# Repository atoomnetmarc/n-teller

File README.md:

# n-teller

n-teller is an IoT device that displays the number of [checked in participants and visitors](https://revspace.nl/N) at the hackerspace called [Revelation Space (or RevSpace)](https://revspace.nl).

It connects to the [RevSpace MQTT server](https://revspace.nl/MQTT) via WiFi using an ESP8266.

The MQTT server publishes to [a few topics of interest](https://revspace.nl/MQTT#Topics) that are subscribed:

- revspace/[doorduino](https://revspace.nl/Doorduino3)/checked-in: this is the current total checked people.
- revspace/[state](https://revspace.nl/Spacestatus): the current state (open or closed) of the hackerspace.

# Schematic

[hardware/n-teller-schematic.pdf](hardware/n-teller-schematic.pdf)

# BOM

See interactive BOM: [hardware/bom/](https://html-preview.github.io/?url=https://github.com/atoomnetmarc/n-teller/blob/main/hardware/bom/ibom.html)

You will also need:

- The pcb. See [hardware/gerber/](hardware/gerber/) for gerber files.
- 2x M3x12 BHCS screws.
- Optional 1x [USB Type-C Female Chassis Connector](USB%20Type-C%20Female%20Chassis%20Connector.jpg).

# Render

# 3d-print

In the [3d](3d/) directory you can find a stand for the pcb.

Print `n-teller-stand-w-usb-c-socket.stl`. This will fit the optional USB Type-C Female Chassis Connector mentioned in the BOM. Or print `n-teller-stand.stl` and roll your own connection to 5V power supply.

# Firmware

Compile and flash the firmware located in the [firmware directory](firmware/). You will need [PlatformIO](https://platformio.org/) for this. I recommend installing the [PlatformIO extension for VSCode](https://platformio.org/install/ide?install=vscode).

# Configure WiFi

Double press the reset button (somewhat slowly). The letters `AP` will appear on the display. Now connect to a WiFi network with a name like `nteller-bcddc2895fd2`. Then go to: http://192.168.4.1/ and configure your WiFi.

# Display information

PCB was designed to fit this type (pinout and dimensions) of 0.36" 4-digit 7-segment common cathode LED display:

## Model numbers and color options

| Model         | Color      | Tested             |
| ------------- | ---------- | ------------------ |
| LFD036AAG-101 | green      |
| 3461AB        | blue       | :heavy_check_mark: |
| 3461AG        | green      |
| 3461AGG       | jade green |
| 3461AO        | orange     |
| 3461AS        | red        |
| 3461AW        | white      |
| 3461AY        | yellow     |

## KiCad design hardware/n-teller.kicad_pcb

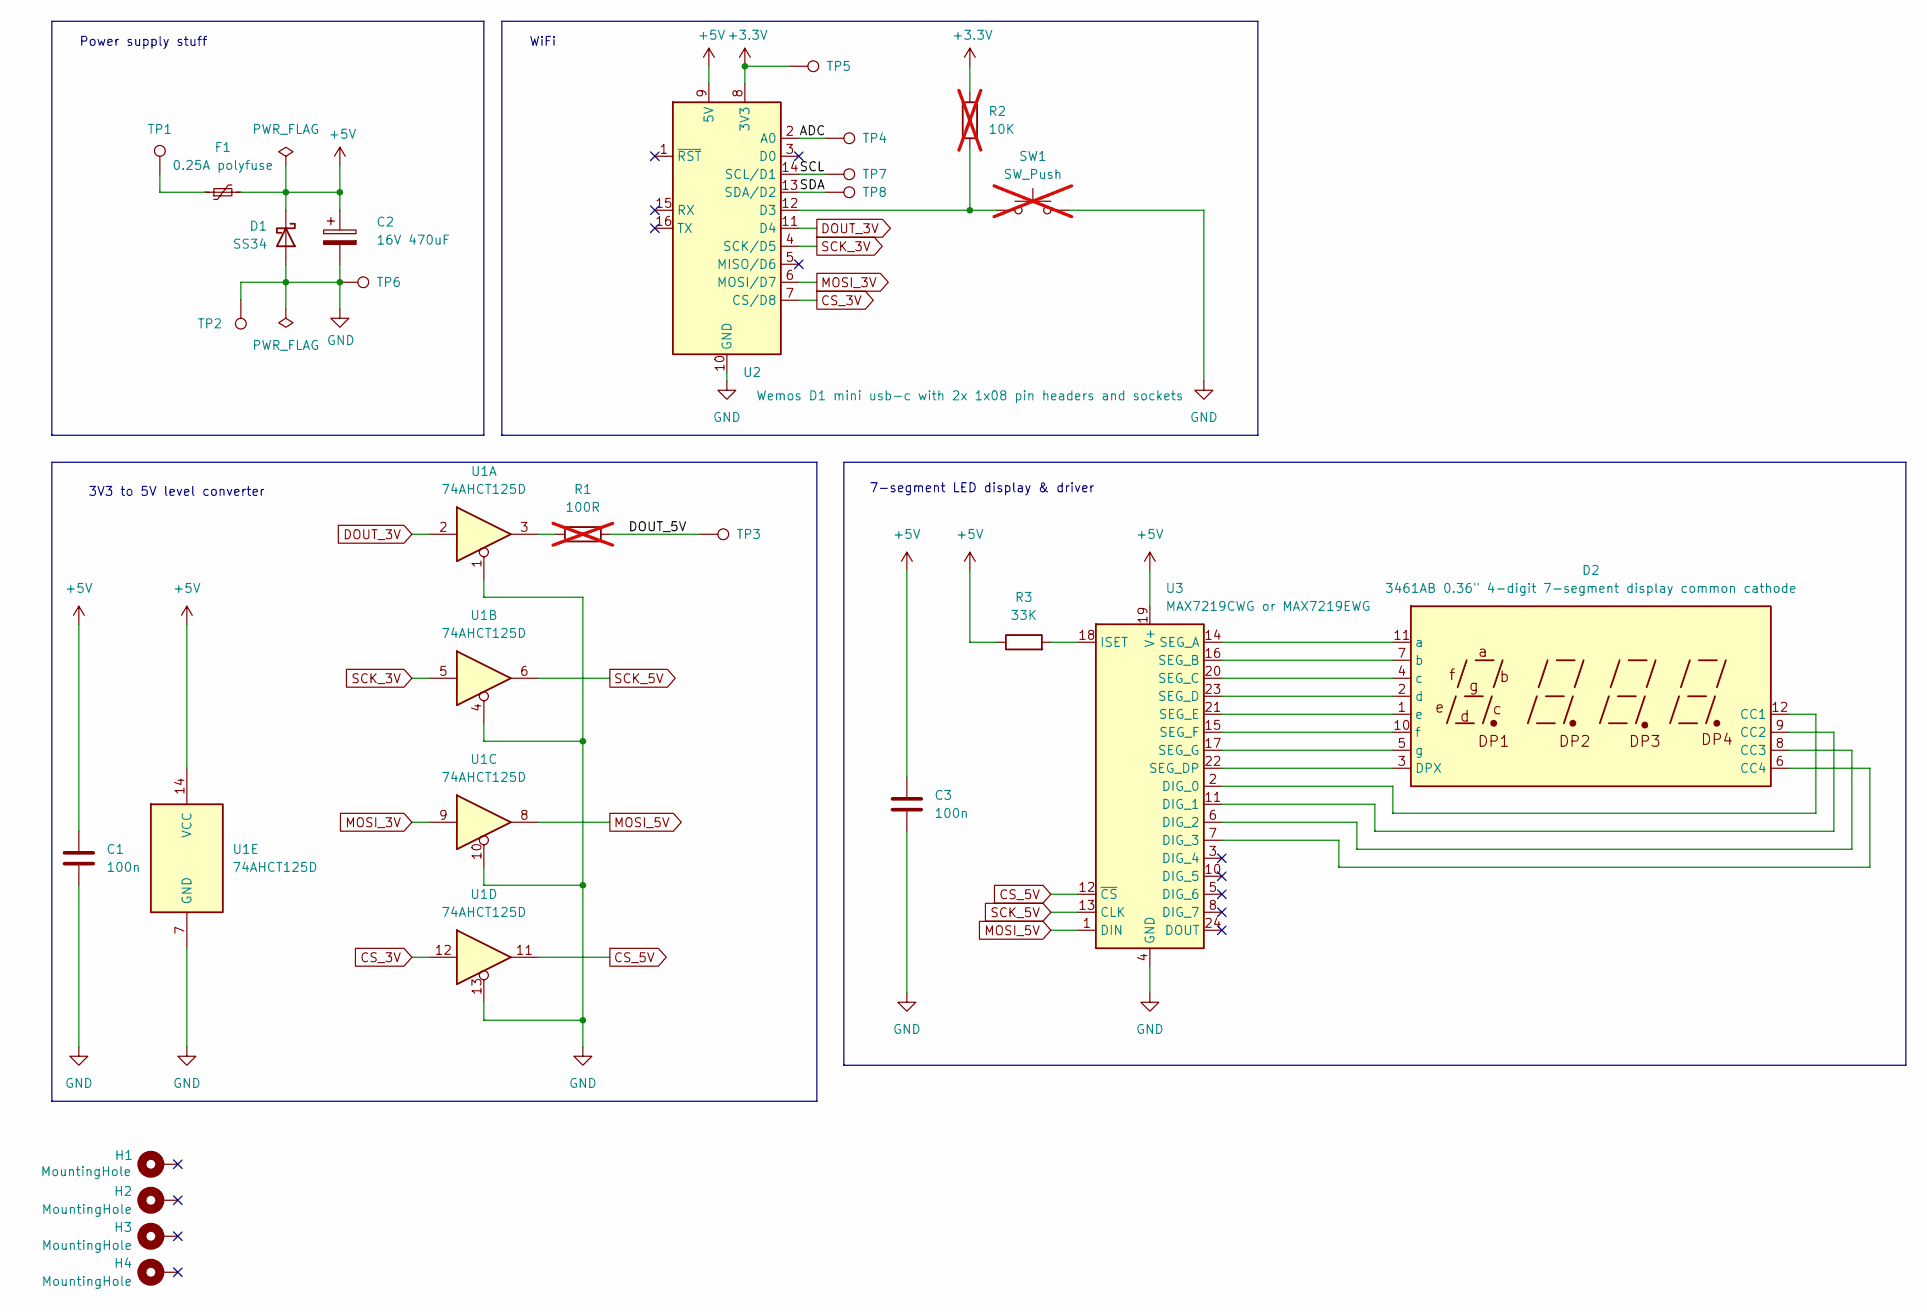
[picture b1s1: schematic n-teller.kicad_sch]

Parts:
C1, C3: 100n; C_0805_2012Metric_Pad1.18x1.45mm_HandSolder
C2: 16V 470uF; CP_Radial_D8.0mm_P3.50mm
D1: SS34; D_SMA
D2: 3461AB 0.36" 4-digit 7-segment display common cat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; 3461
F1: 0.25A polyfuse; Fuse_1206_3216Metric_Pad1.42x1.75mm_HandSolder
H1, H2, H3, H4: MountingHole; MountingHole_3.2mm_M3_Pad_Via
R1: 100R; R_0805_2012Metric_Pad1.20x1.40mm_HandSolder; not fitted
R2: 10K; R_0805_2012Metric_Pad1.20x1.40mm_HandSolder; not fitted
R3: 33K; R_0805_2012Metric_Pad1.20x1.40mm_HandSolder
SW1: SW_Push; SW_SPST_CK_RS282G05A3; not fitted
TP1, TP2: TestPoint; TestPoint_Pad_D4.0mm
TP3, TP4, TP5, TP6: TestPoint; TestPoint_Pad_D2.0mm
TP7, TP8: TestPoint; TestPoint_Pad_D1.0mm
U1: 74AHCT125D; SOIC-14_3.9x8.7mm_P1.27mm
U2: Wemos D1 mini usb-c with 2x 1x08 pin headers and 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; WEMOS_D1_mini
U3: MAX7219CWG or MAX7219EWG; SOIC-24W_7.5x15.4mm_P1.27mm

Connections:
+3.3V: R2.2, TP5.1, U2.8 (3V3)
+5V: C1.1, C2.1, C3.1, D1.1 (K), F1.2, R3.1, U1.14 (VCC), U2.9 (5V), U3.19 (V+)
/ADC: TP4.1, U2.2 (A0)
/DOUT_5V: R1.2, TP3.1
/SCL: TP7.1, U2.14 (SCL/D1)
/SDA: TP8.1, U2.13 (SDA/D2)
CS_3V: U1.12, U2.7 (CS/D8)
CS_5V: U1.11, U3.12 (~CS)
DOUT_3V: U1.2, U2.11 (D4)
GND: C1.2, C2.2, C3.2, D1.2 (A), SW1.1, TP2.1, TP6.1, U1.1, U1.4, U1.7 (GND), U1.10, U1.13, U2.10 (GND), U3.4 (GND), U3.9 (GND)
MOSI_3V: U1.9, U2.6 (MOSI/D7)
MOSI_5V: U1.8, U3.1 (DIN)
unnamed: D2.12 (CC1), U3.2 (DIG_0)
unnamed: D2.9 (CC2), U3.11 (DIG_1)
unnamed: D2.8 (CC3), U3.6 (DIG_2)
unnamed: D2.6 (CC4), U3.7 (DIG_3)
unnamed: D2.3 (DPX), U3.22 (SEG_DP)
unnamed: D2.11 (a), U3.14 (SEG_A)
unnamed: D2.7 (b), U3.16 (SEG_B)
unnamed: D2.4 (c), U3.20 (SEG_C)
unnamed: D2.2 (d), U3.23 (SEG_D)
unnamed: D2.1 (e), U3.21 (SEG_E)
unnamed: D2.10 (f), U3.15 (SEG_F)
unnamed: D2.5 (g), U3.17 (SEG_G)
unnamed: F1.1, TP1.1
unnamed: R1.1, U1.3
unnamed: R2.1, SW1.2, U2.12 (D3)
unnamed: R3.2, U3.18 (ISET)
SCK_3V: U1.5, U2.4 (SCK/D5)
SCK_5V: U1.6, U3.13 (CLK)

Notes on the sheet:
7-segment LED display & driver
3V3 to 5V level converter
Power supply stuff
WiFi

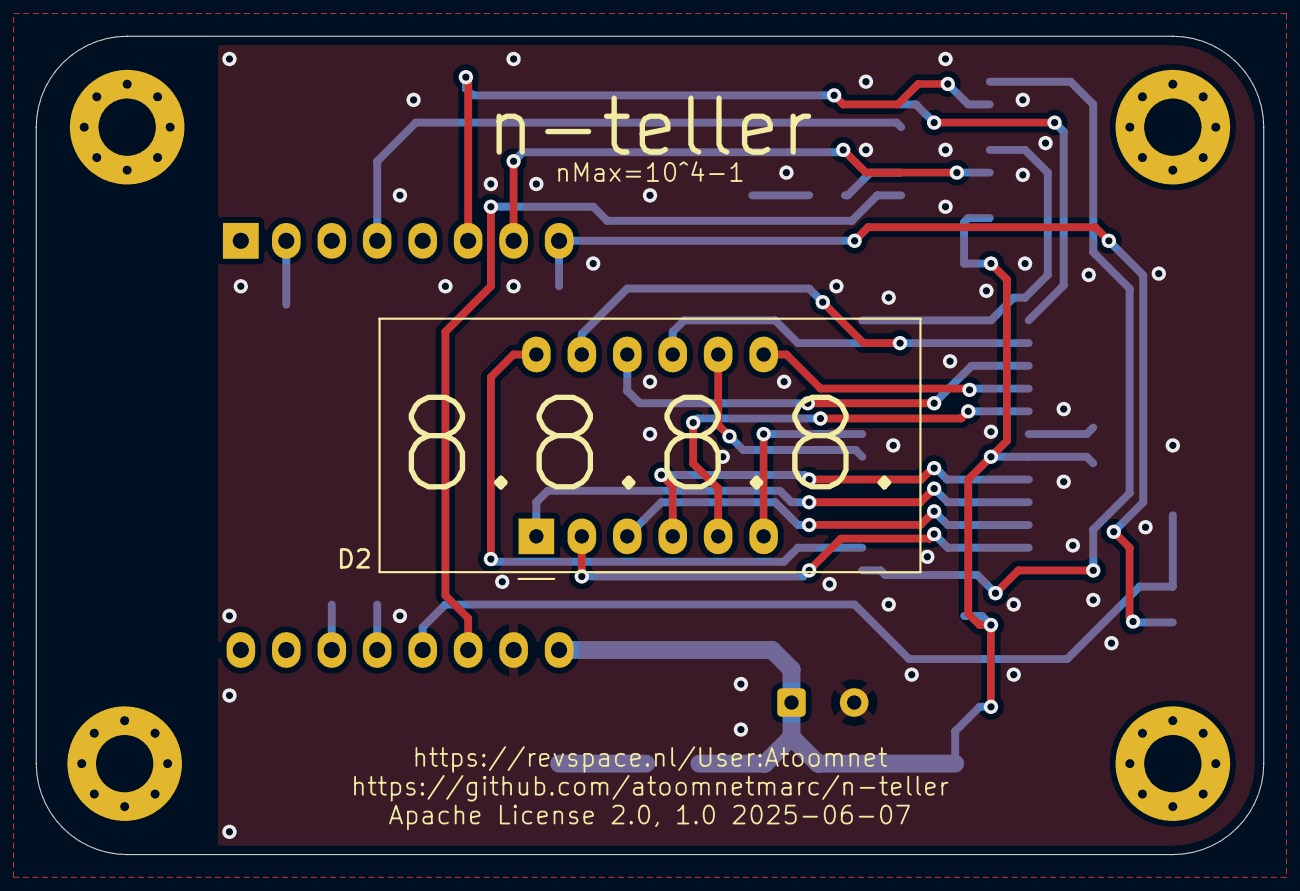
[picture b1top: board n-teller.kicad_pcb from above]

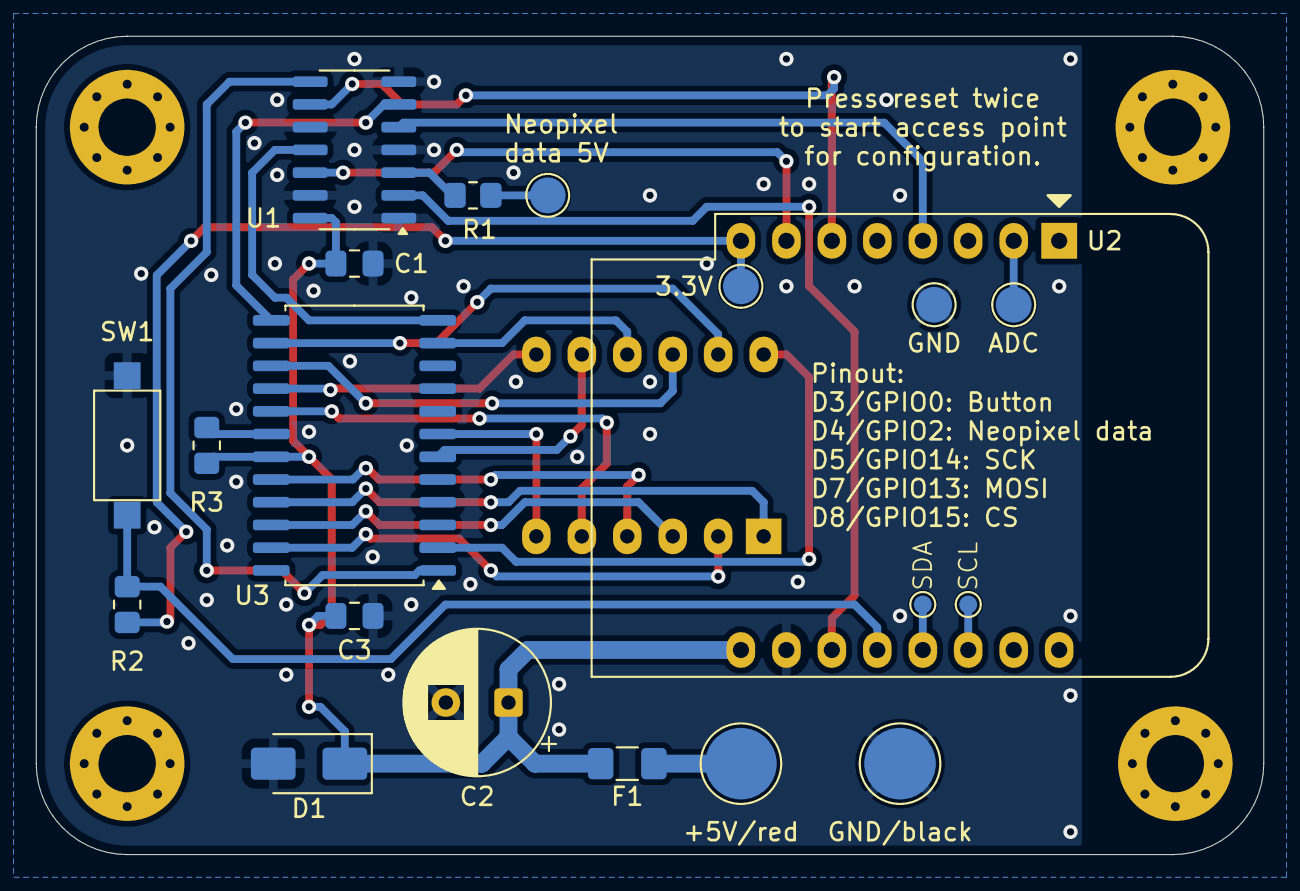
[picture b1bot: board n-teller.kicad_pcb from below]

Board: 2 copper layers, 68.6 x 45.7 mm, 25 parts (20 on the bottom side), 30 nets.

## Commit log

2025-06-26 Switch MAX7219 libraries.
2025-06-27 Connect to WiFi and MQTT.
2025-06-27 Pics or did not happen.
2025-06-27 Refactor.
2025-06-27 Update display model table.
2025-06-28 Show n= while closed.
2025-06-28 Render digit pattern more elegantly.
2025-07-06 Increase WiFi config timeout.
2025-07-11 Fix typo in definition of bitmap for 'c'
2025-07-12 Initial work to load the time
    Modifications so the devices loads the time from NTP and (so far) spits it to serial
2025-07-12 Extend DisplayManager to store data and flip modes
2025-07-22 Add orange model number.
2025-09-06 Improve grammar.
2025-09-21 Make ibom viewable in browser.
2026-01-23 Add CONTRIBUTING.md

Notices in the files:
README.md:
License: Apache 2.0
hardware/n-teller.kicad_pcb:
Apache License 2.0
